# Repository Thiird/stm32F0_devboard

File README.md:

# STM32F03 Dev board

To flash the board use:

`stm32flash -b 115200 -i -rts,dtr:-dtr,rts -w ./program.bin /dev/ttyUSB0`

Make sure to use the appropriate path to the .bin you want to flash and change `ttyUSBO` to whatever your system assigned to the dev board.

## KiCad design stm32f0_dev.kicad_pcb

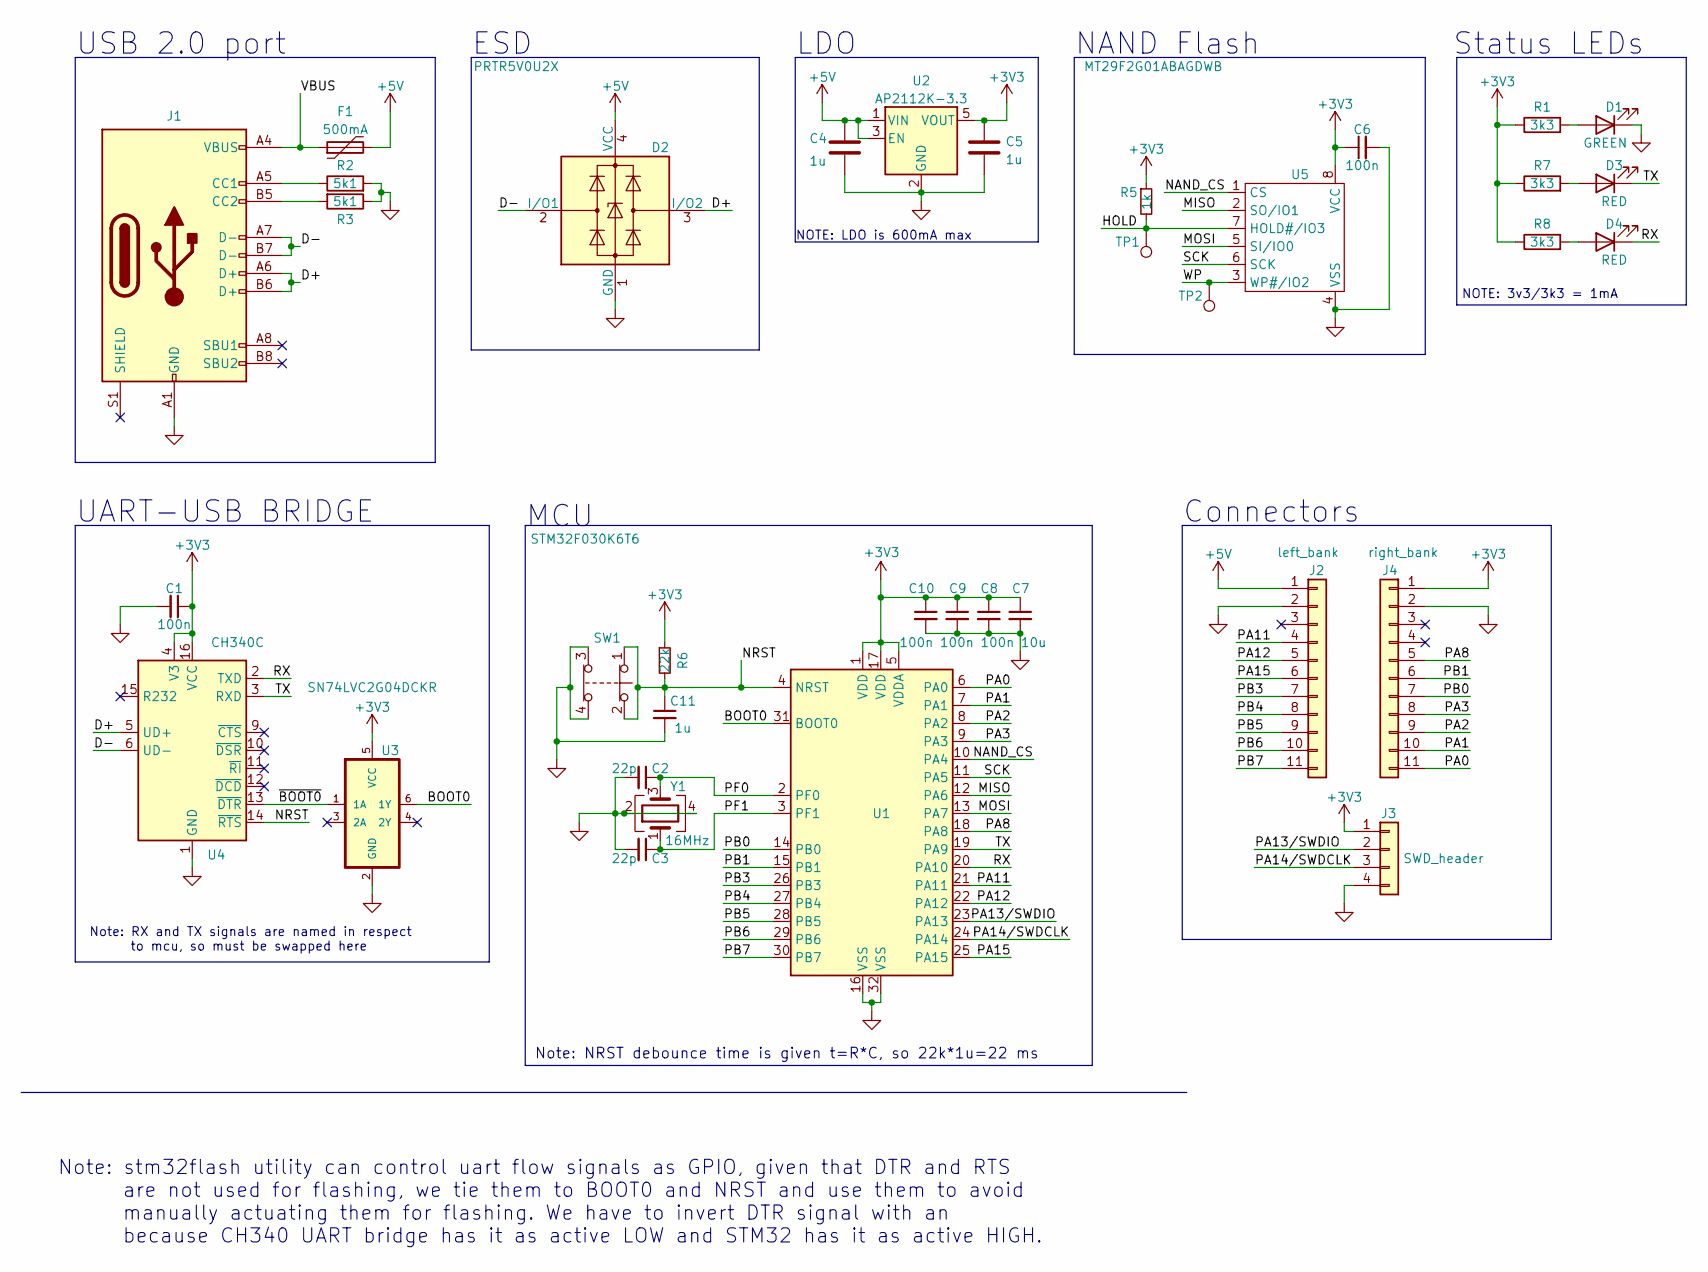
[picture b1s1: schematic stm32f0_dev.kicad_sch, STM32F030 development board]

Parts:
C1, C6, C8, C9, C10: 100n; C_0603_1608Metric
C2, C3: 22p; C_0603_1608Metric
C4, C5, C11: 1u; C_0603_1608Metric
C7: 10u; C_0603_1608Metric
D1: GREEN; LED_0603_1608Metric
D2: PRTR5V0U2X; SOT-143
D3, D4: RED; LED_0603_1608Metric
F1: 500mA; Fuse_0603_1608Metric
J1: USB_C_Receptacle_USB2.0; USB_C_Receptacle_HRO_TYPE-C-31-M-12
J2: left_bank; PinHeader_1x11_P2.54mm_Vertical
J3: SWD_header; PinHeader_1x04_P2.54mm_Vertical
J4: right_bank; PinHeader_1x11_P2.54mm_Vertical
R1, R7, R8: 3k3; R_0603_1608Metric
R2, R3: 5k1; R_0603_1608Metric
R5: 1k; R_0603_1608Metric
R6: 22k; R_0603_1608Metric
SW1: SW_Push_Open_Dual; SW_SKRPACE010
TP1, TP2: TestPoint; TestPoint_Pad_D1.0mm
U1: STM32F030K6T6; LQFP-32_7x7mm_P0.8mm
U2: AP2112K-3.3; SOT-23-5
U3: SN74LVC2G04DCKR; SOT65P210X110-6N
U4: CH340C; SOIC-16_3.9x9.9mm_P1.27mm
U5: MT29F2G01ABAGDWB; SON127P600X800X65-8N
Y1: 16MHz; Crystal_SMD_2016-4Pin_2.0x1.6mm

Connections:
+3V3: C1.1, C5.1, C6.1, C7.1, C8.1, C9.1, C10.1, J3.1, J4.1, R1.1, R5.1, R6.1, R7.1, R8.1, U1.1 (VDD), U1.5 (VDDA), U1.17 (VDD), U2.5 (VOUT), U3.5 (VCC), U4.4 (V3), U4.16 (VCC), U5.8 (VCC)
+5V: C4.1, D2.4 (VCC), F1.2, J2.1, U2.1 (VIN), U2.3 (EN)
/BOOT0: U1.31 (BOOT0), U3.6 (1Y)
/D+: D2.3 (I/O2), J1.A6 (D+), J1.B6 (D+), U4.5 (UD+)
/D-: D2.2 (I/O1), J1.A7 (D-), J1.B7 (D-), U4.6 (UD-)
/HOLD: R5.2, TP1.1, U5.7 (HOLD#/IO3)
/MISO: U1.12 (PA6), U5.2 (SO/IO1)
/MOSI: U1.13 (PA7), U5.5 (SI/IO0)
/NAND_CS: U1.10 (PA4), U5.1 (CS)
/NRST: C11.1, R6.2, SW1.1, SW1.2, U1.4 (NRST), U4.14 (~RTS)
/PA0: J4.11, U1.6 (PA0)
/PA1: J4.10, U1.7 (PA1)
/PA2: J4.9, U1.8 (PA2)
/PA3: J4.8, U1.9 (PA3)
/PA8: J4.5, U1.18 (PA8)
/PA11: J2.4, U1.21 (PA11)
/PA12: J2.5, U1.22 (PA12)
/PA13/SWDIO: J3.2, U1.23 (PA13)
/PA14/SWDCLK: J3.3, U1.24 (PA14)
/PA15: J2.6, U1.25 (PA15)
/PB0: J4.7, U1.14 (PB0)
/PB1: J4.6, U1.15 (PB1)
/PB3: J2.7, U1.26 (PB3)
/PB4: J2.8, U1.27 (PB4)
/PB5: J2.9, U1.28 (PB5)
/PB6: J2.10, U1.29 (PB6)
/PB7: J2.11, U1.30 (PB7)
/PF0: C2.1, U1.2 (PF0), Y1.3
/PF1: C3.1, U1.3 (PF1), Y1.1
/RX: D4.1 (K), U1.20 (PA10), U4.2 (TXD)
/SCK: U1.11 (PA5), U5.6 (SCK)
/TX: D3.1 (K), U1.19 (PA9), U4.3 (RXD)
/VBUS: F1.1, J1.A4 (VBUS), J1.A9 (VBUS), J1.B4 (VBUS), J1.B9 (VBUS)
/WP: TP2.1, U5.3 (WP#/IO2)
/~BOOT0: U3.1 (1A), U4.13 (~DTR)
GND: C1.2, C2.2, C3.2, C4.2, C5.2, C6.2, C7.2, C8.2, C9.2, C10.2, C11.2, D1.1 (K), D2.1 (GND), J1.A1 (GND), J1.A12 (GND), J1.B1 (GND), J1.B12 (GND), J2.2, J3.4, J4.2, R2.2, R3.1, SW1.3, SW1.4, U1.16 (VSS), U1.32 (VSS), U2.2 (GND), U3.2 (GND), U4.1 (GND), U5.4 (VSS), Y1.2, Y1.4
unnamed: D1.2 (A), R1.2
unnamed: D3.2 (A), R7.2
unnamed: D4.2 (A), R8.2
unnamed: J1.A5 (CC1), R2.1
unnamed: J1.B5 (CC2), R3.2

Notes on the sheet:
NAND Flash
ESD
NOTE: LDO is 600mA max
LDO
UART-USB BRIDGE
MCU
Note: stm32flash utility can control uart flow signals as GPIO, given that DTR and RTS are not used for flashing, we tie them to BOOT0 and NRST and use them to avoid manually actuating them for flashing. We have to invert DTR signal with an because CH340 UART bridge has it as active LOW and STM32 h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
Connectors
Note: RX and TX signals are named in respect to mcu, so must be swapped here
USB 2.0 port
NOTE: 3v3/3k3 = 1mA
Note: NRST debounce time is given t=R*C, so 22k*1u=22 ms
Status LEDs

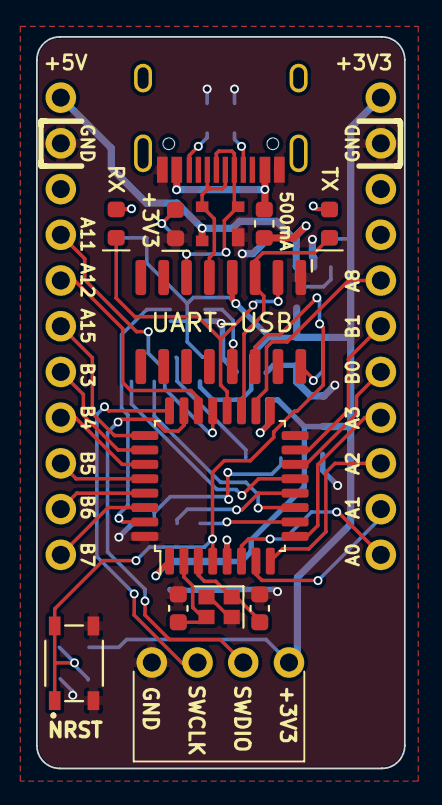
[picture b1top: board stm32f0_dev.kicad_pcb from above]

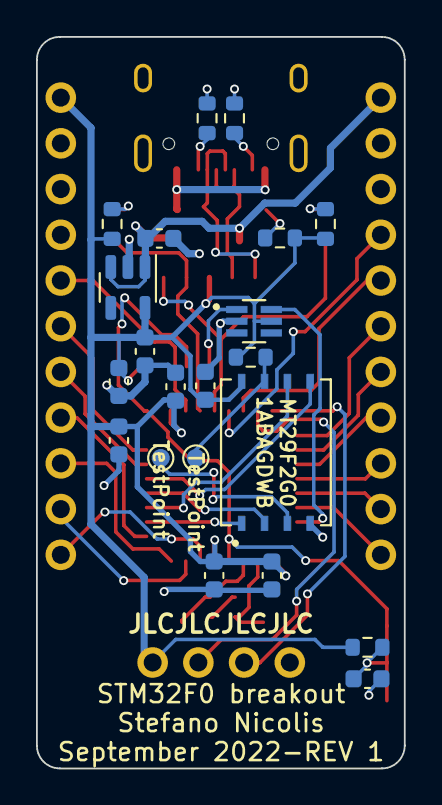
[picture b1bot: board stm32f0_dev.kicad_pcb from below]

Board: 2 copper layers, 20.4 x 40.6 mm, 36 parts (21 on the bottom side), 41 nets.

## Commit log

2022-08-30 First commit, board mostly complete
2022-08-31 Schematic done, routing done, to fix issues on board
2022-09-02 Finished board, added gerber folder, uart leds, board dimensions
2022-09-20 Fixed nrst button, dtr signal
2022-10-26 Added README
2022-10-26 Removed useless boot0 switch, uart IC is driving that signal
